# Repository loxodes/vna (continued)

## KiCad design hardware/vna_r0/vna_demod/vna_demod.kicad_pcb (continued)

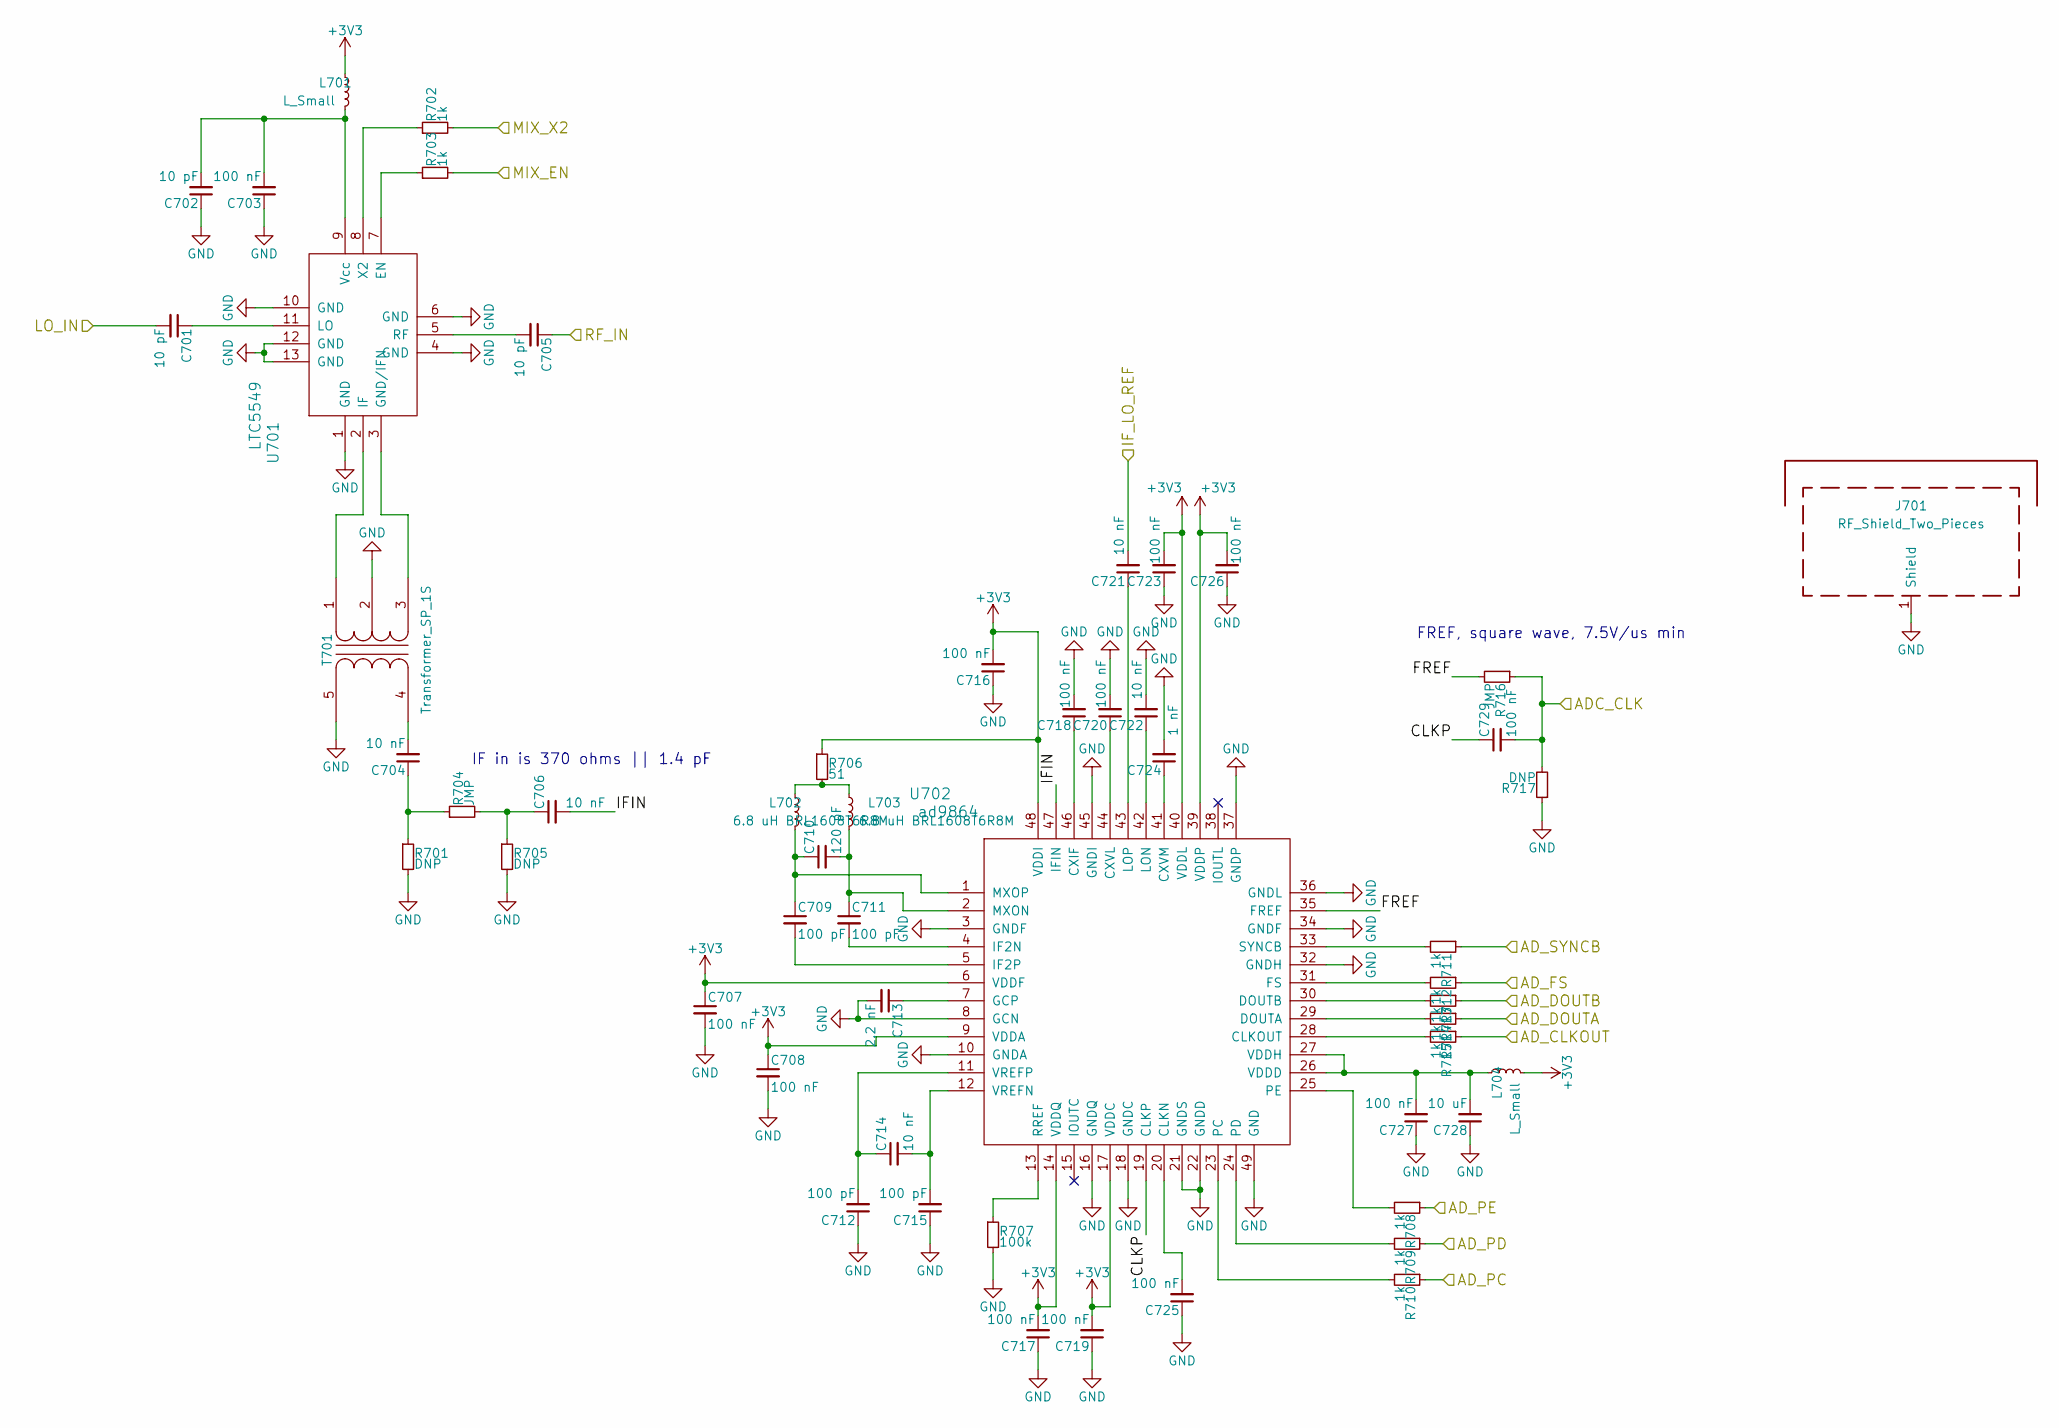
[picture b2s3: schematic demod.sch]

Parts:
C301, C302, C305: 10 pF; C_0402
C303, C307, C308, C316, C317, C318, C319, C320, C323, C325, C326, C327, C329: 100 nF; C_0402
C304, C306, C314, C321, C322: 10 nF; C_0402
C309, C311, C312, C315: 100 pF; C_0402
C310: 120 pF; C_0402
C313: 2.2 nF; C_0402
C324: 1 nF; C_0402
C328: 10 uF; C_0603
J301: RF_Shield_Two_Pieces; Laird_Technologies_BMI-S-209-F_29.36x18.50mm
L301, L304: L_Small; R_0402
L302, L303: 6.8 uH BRL1608T6R8M; R_0603
R301, R305, R317: DNP; R_0402
R302, R303, R308, R309, R310, R311, R312, R313, R314, R315: 1k; R_0402
R304, R316: JMP; R_0402
R306: 51; R_0402
R307: 100k; R_0402
T301: Transformer_SP_1S; 5LEAD_BALUN_4p83mm_3p3mm
U301: LTC5549; QFN_12_3mm2mm
U302: ad9864; QFN-48-1EP_7x7mm_Pitch0.5mm

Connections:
+3V3: C307.1, C308.1, C316.2, C317.2, C319.2, C323.2, C326.2, L301.1, L304.2, R306.1, U302.6 (VDDF), U302.9 (VDDA), U302.14 (VDDQ), U302.17 (VDDC), U302.39 (VDDP), U302.40 (VDDL), U302.48 (VDDI); also elsewhere on the board
/ADC_CLK_A: C329.2, R316.1, R317.2; also elsewhere on the board
/AD_CLKOUT: R315.1; also elsewhere on the board
/AD_DOUTA_A: R314.1; also elsewhere on the board
/AD_DOUTB: R313.1; also elsewhere on the board
/AD_FS: R312.1; also elsewhere on the board
/AD_PC: R310.1; also elsewhere on the board
/AD_PD: R309.1; also elsewhere on the board
/AD_PE_A: R308.1; also elsewhere on the board
/AD_SYNCB: R311.1; also elsewhere on the board
/IF_LO_REF_A: C321.2; also elsewhere on the board
/MIX_EN: R303.2; also elsewhere on the board
/MIX_X2: R302.2; also elsewhere on the board
/conn_power/RF_A: C305.1; also elsewhere on the board
/demod_A/CLKP: C329.1, U302.19 (CLKP)
/demod_A/FREF: R316.2, U302.35 (FREF)
/demod_A/IFIN: C306.2, U302.47 (IFIN)
/lo_synth/LO_A: C301.2; also elsewhere on the board
GND: C302.1, C303.1, C307.2, C308.2, C312.1, C313.2, C315.1, C316.1, C317.1, C318.2, C319.1, C320.2, C322.2, C323.1, C324.2, C325.1, C326.1, C327.1, C328.1, J301.1, R301.2, R305.2, R307.2, R317.1, T301.2 (PM), T301.5 (S2), U301.1 (GND), U301.4 (GND), U301.6 (GND), U301.10 (GND), U301.12 (GND), U301.13 (GND), U302.3 (GNDF), U302.8 (GCN), U302.10 (GNDA), U302.16 (GNDQ), U302.18 (GNDC), U302.21 (GNDS), U302.22 (GNDD), U302.32 (GNDH), U302.34 (GNDF), U302.36 (GNDL), U302.37 (GNDP), U302.45 (GNDI), U302.49 (GND); also elsewhere on the board
unnamed: C301.1, U301.11 (LO)
unnamed: C302.2, C303.2, L301.2, U301.9 (Vcc)
unnamed: C304.1, R301.1, R304.1
unnamed: C304.2, T301.4 (S1)
unnamed: C305.2, U301.5 (RF)
unnamed: C306.1, R304.2, R305.1
unnamed: C309.1, C310.1, L302.2, U302.1 (MXOP)
unnamed: C309.2, U302.5 (IF2P)
unnamed: C310.2, C311.1, L303.2, U302.2 (MXON)
unnamed: C311.2, U302.4 (IF2N)
unnamed: C312.2, C314.1, U302.11 (VREFP)
unnamed: C313.1, U302.7 (GCP)
unnamed: C314.2, C315.2, U302.12 (VREFN)
unnamed: C318.1, U302.46 (CXIF)
unnamed: C320.1, U302.44 (CXVL)
unnamed: C321.1, U302.43 (LOP)
unnamed: C322.1, U302.42 (LON)
unnamed: C324.1, U302.41 (CXVM)
unnamed: C325.2, U302.20 (CLKN)
unnamed: C327.2, C328.2, L304.1, U302.26 (VDDD), U302.27 (VDDH)
unnamed: L302.1, L303.1, R306.2
unnamed: R302.1, U301.8 (X2)
unnamed: R303.1, U301.7 (EN)
unnamed: R307.1, U302.13 (RREF)
unnamed: R308.2, U302.25 (PE)
unnamed: R309.2, U302.24 (PD)
unnamed: R310.2, U302.23 (PC)
unnamed: R311.2, U302.33 (SYNCB)
unnamed: R312.2, U302.31 (FS)
unnamed: R313.2, U302.30 (DOUTB)
unnamed: R314.2, U302.29 (DOUTA)
unnamed: R315.2, U302.28 (CLKOUT)
unnamed: T301.1 (PR1), U301.2 (IF)
unnamed: T301.3 (PR2), U301.3 (GND/IFN)

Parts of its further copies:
C501, C502, C505, C601, C602, C605, C701, C702, C705: 10 pF; C_0402
C503, C507, C508, C516, C517, C518, C519, C520, C523, C525, C526, C527, C529, C603, C607, C608, C616, C617, C618, C619, C620, C623, C625, C626, C627, C629, C703, C707, C708, C716, C717, C718, C719, C720, C723, C725, C726, C727, C729: 100 nF; C_0402
C504, C506, C514, C521, C522, C604, C606, C614, C621, C622, C704, C706, C714, C721, C722: 10 nF; C_0402
C509, C511, C512, C515, C609, C611, C612, C615, C709, C711, C712, C715: 100 pF; C_0402
C510, C610, C710: 120 pF; C_0402
C513, C613, C713: 2.2 nF; C_0402
C524, C624, C724: 1 nF; C_0402
C528, C628, C728: 10 uF; C_0603
J501, J601, J701: RF_Shield_Two_Pieces; Laird_Technologies_BMI-S-209-F_29.36x18.50mm
L501, L504, L601, L604, L701, L704: L_Small; R_0402
L502, L503, L602, L603, L702, L703: 6.8 uH BRL1608T6R8M; R_0603
R501, R505, R517, R601, R605, R617, R701, R705, R717: DNP; R_0402
R502, R503, R508, R509, R510, R511, R512, R513, R514, R515, R602, R603, R608, R609, R610, R611, R612, R613, R614, R615, R702, R703, R708, R709, R710, R711, R712, R713, R714, R715: 1k; R_0402
R504, R516, R604, R616, R704, R716: JMP; R_0402
R506, R606, R706: 51; R_0402
R507, R607, R707: 100k; R_0402
T501, T601, T701: Transformer_SP_1S; 5LEAD_BALUN_4p83mm_3p3mm
U501, U601, U701: LTC5549; QFN_12_3mm2mm
U502, U602, U702: ad9864; QFN-48-1EP_7x7mm_Pitch0.5mm

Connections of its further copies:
+3V3: C507.1, C508.1, C516.2, C517.2, C519.2, C523.2, C526.2, C607.1, C608.1, C616.2, C617.2, C619.2, C623.2, C626.2, C707.1, C708.1, C716.2, C717.2, C719.2, C723.2, C726.2, L501.1, L504.2, L601.1, L604.2, L701.1, L704.2, R506.1, R606.1, R706.1, U502.6 (VDDF), U502.9 (VDDA), U502.14 (VDDQ), U502.17 (VDDC), U502.39 (VDDP), U502.40 (VDDL), U502.48 (VDDI), U602.6 (VDDF), U602.9 (VDDA), U602.14 (VDDQ), U602.17 (VDDC), U602.39 (VDDP), U602.40 (VDDL), U602.48 (VDDI), U702.6 (VDDF), U702.9 (VDDA), U702.14 (VDDQ), U702.17 (VDDC), U702.39 (VDDP), U702.40 (VDDL), U702.48 (VDDI); also elsewhere on the board
/ADC_CLK_B: C529.2, R516.1, R517.2; also elsewhere on the board
/ADC_CLK_C: C629.2, R616.1, R617.2; also elsewhere on the board
/ADC_CLK_D: C729.2, R716.1, R717.2; also elsewhere on the board
/AD_DOUTA_B: R514.1; also elsewhere on the board
/AD_DOUTA_C: R614.1; also elsewhere on the board
/AD_DOUTA_D: R714.1; also elsewhere on the board
/AD_DOUTB: R513.1, R613.1, R713.1; also elsewhere on the board
/AD_PC: R510.1, R610.1, R710.1; also elsewhere on the board
/AD_PD: R509.1, R609.1, R709.1; also elsewhere on the board
/AD_PE_B: R508.1; also elsewhere on the board
/AD_PE_C: R608.1; also elsewhere on the board
/AD_PE_D: R708.1; also elsewhere on the board
/AD_SYNCB: R511.1, R611.1, R711.1; also elsewhere on the board
/IF_LO_REF_B: C521.2; also elsewhere on the board
/IF_LO_REF_C: C621.2; also elsewhere on the board
/IF_LO_REF_D: C721.2; also elsewhere on the board
/MIX_EN: R503.2, R603.2, R703.2; also elsewhere on the board
/MIX_X2: R502.2, R602.2, R702.2; also elsewhere on the board
/conn_power/RF_B: C505.1; also elsewhere on the board
/conn_power/RF_C: C605.1; also elsewhere on the board
/conn_power/RF_D: C705.1; also elsewhere on the board
/demod_B/CLKP: C529.1, U502.19 (CLKP)
/demod_B/FREF: R516.2, U502.35 (FREF)
/demod_B/IFIN: C506.2, U502.47 (IFIN)
/demod_C/CLKP: C629.1, U602.19 (CLKP)
/demod_C/FREF: R616.2, U602.35 (FREF)
/demod_C/IFIN: C606.2, U602.47 (IFIN)
/demod_D/CLKP: C729.1, U702.19 (CLKP)
/demod_D/FREF: R716.2, U702.35 (FREF)
/demod_D/IFIN: C706.2, U702.47 (IFIN)
/lo_synth/LO_B: C501.2; also elsewhere on the board
/lo_synth/LO_C: C601.2; also elsewhere on the board
/lo_synth/LO_D: C701.2; also elsewhere on the board
GND: C502.1, C503.1, C507.2, C508.2, C512.1, C513.2, C515.1, C516.1, C517.1, C518.2, C519.1, C520.2, C522.2, C523.1, C524.2, C525.1, C526.1, C527.1, C528.1, C602.1, C603.1, C607.2, C608.2, C612.1, C613.2, C615.1, C616.1, C617.1, C618.2, C619.1, C620.2, C622.2, C623.1, C624.2, C625.1, C626.1, C627.1, C628.1, C702.1, C703.1, C707.2, C708.2, C712.1, C713.2, C715.1, C716.1, C717.1, C718.2, C719.1, C720.2, C722.2, C723.1, C724.2, C725.1, C726.1, C727.1, C728.1, J501.1, J601.1, J701.1, R501.2, R505.2, R507.2, R517.1, R601.2, R605.2, R607.2, R617.1, R701.2, R705.2, R707.2, R717.1, T501.2 (PM), T501.5 (S2), T601.2 (PM), T601.5 (S2), T701.2 (PM), T701.5 (S2), U501.1 (GND), U501.4 (GND), U501.6 (GND), U501.10 (GND), U501.12 (GND), U501.13 (GND), U502.3 (GNDF), U502.8 (GCN), U502.10 (GNDA), U502.16 (GNDQ), U502.18 (GNDC), U502.21 (GNDS), U502.22 (GNDD), U502.32 (GNDH), U502.34 (GNDF), U502.36 (GNDL), U502.37 (GNDP), U502.45 (GNDI), U502.49 (GND), U601.1 (GND), U601.4 (GND), U601.6 (GND), U601.10 (GND), U601.12 (GND), U601.13 (GND), U602.3 (GNDF), U602.8 (GCN), U602.10 (GNDA), U602.16 (GNDQ), U602.18 (GNDC), U602.21 (GNDS), U602.22 (GNDD), U602.32 (GNDH), U602.34 (GNDF), U602.36 (GNDL), U602.37 (GNDP), U602.45 (GNDI), U602.49 (GND), U701.1 (GND), U701.4 (GND), U701.6 (GND), U701.10 (GND), U701.12 (GND), U701.13 (GND), U702.3 (GNDF), U702.8 (GCN), U702.10 (GNDA), U702.16 (GNDQ), U702.18 (GNDC), U702.21 (GNDS), U702.22 (GNDD), U702.32 (GNDH), U702.34 (GNDF), U702.36 (GNDL), U702.37 (GNDP), U702.45 (GNDI), U702.49 (GND); also elsewhere on the board
unnamed: C501.1, U501.11 (LO)
unnamed: C502.2, C503.2, L501.2, U501.9 (Vcc)
unnamed: C504.1, R501.1, R504.1
unnamed: C504.2, T501.4 (S1)
unnamed: C505.2, U501.5 (RF)
unnamed: C506.1, R504.2, R505.1
unnamed: C509.1, C510.1, L502.2, U502.1 (MXOP)
unnamed: C509.2, U502.5 (IF2P)
unnamed: C510.2, C511.1, L503.2, U502.2 (MXON)
unnamed: C511.2, U502.4 (IF2N)
unnamed: C512.2, C514.1, U502.11 (VREFP)
unnamed: C513.1, U502.7 (GCP)
unnamed: C514.2, C515.2, U502.12 (VREFN)
unnamed: C518.1, U502.46 (CXIF)
unnamed: C520.1, U502.44 (CXVL)
unnamed: C521.1, U502.43 (LOP)
unnamed: C522.1, U502.42 (LON)
unnamed: C524.1, U502.41 (CXVM)
unnamed: C525.2, U502.20 (CLKN)
unnamed: C527.2, C528.2, L504.1, U502.26 (VDDD), U502.27 (VDDH)
unnamed: C601.1, U601.11 (LO)
unnamed: C602.2, C603.2, L601.2, U601.9 (Vcc)
unnamed: C604.1, R601.1, R604.1
unnamed: C604.2, T601.4 (S1)
unnamed: C605.2, U601.5 (RF)
unnamed: C606.1, R604.2, R605.1
unnamed: C609.1, C610.1, L602.2, U602.1 (MXOP)
unnamed: C609.2, U602.5 (IF2P)
unnamed: C610.2, C611.1, L603.2, U602.2 (MXON)
unnamed: C611.2, U602.4 (IF2N)
unnamed: C612.2, C614.1, U602.11 (VREFP)
unnamed: C613.1, U602.7 (GCP)
unnamed: C614.2, C615.2, U602.12 (VREFN)
unnamed: C618.1, U602.46 (CXIF)
unnamed: C620.1, U602.44 (CXVL)
unnamed: C621.1, U602.43 (LOP)
unnamed: C622.1, U602.42 (LON)
unnamed: C624.1, U602.41 (CXVM)
unnamed: C625.2, U602.20 (CLKN)
unnamed: C627.2, C628.2, L604.1, U602.26 (VDDD), U602.27 (VDDH)
unnamed: C701.1, U701.11 (LO)
unnamed: C702.2, C703.2, L701.2, U701.9 (Vcc)
unnamed: C704.1, R701.1, R704.1
unnamed: C704.2, T701.4 (S1)
unnamed: C705.2, U701.5 (RF)
unnamed: C706.1, R704.2, R705.1
unnamed: C709.1, C710.1, L702.2, U702.1 (MXOP)
unnamed: C709.2, U702.5 (IF2P)
unnamed: C710.2, C711.1, L703.2, U702.2 (MXON)
unnamed: C711.2, U702.4 (IF2N)
unnamed: C712.2, C714.1, U702.11 (VREFP)
unnamed: C713.1, U702.7 (GCP)
unnamed: C714.2, C715.2, U702.12 (VREFN)
unnamed: C718.1, U702.46 (CXIF)
unnamed: C720.1, U702.44 (CXVL)
unnamed: C721.1, U702.43 (LOP)
unnamed: C722.1, U702.42 (LON)
unnamed: C724.1, U702.41 (CXVM)
unnamed: C725.2, U702.20 (CLKN)
unnamed: C727.2, C728.2, L704.1, U702.26 (VDDD), U702.27 (VDDH)
unnamed: L502.1, L503.1, R506.2
unnamed: L602.1, L603.1, R606.2
unnamed: L702.1, L703.1, R706.2
unnamed: R502.1, U501.8 (X2)
unnamed: R503.1, U501.7 (EN)
unnamed: R507.1, U502.13 (RREF)
unnamed: R508.2, U502.25 (PE)
unnamed: R509.2, U502.24 (PD)
unnamed: R510.2, U502.23 (PC)
unnamed: R511.2, U502.33 (SYNCB)
unnamed: R512.2, U502.31 (FS)
unnamed: R513.2, U502.30 (DOUTB)
unnamed: R514.2, U502.29 (DOUTA)
unnamed: R515.2, U502.28 (CLKOUT)
unnamed: R602.1, U601.8 (X2)
unnamed: R603.1, U601.7 (EN)
unnamed: R607.1, U602.13 (RREF)
unnamed: R608.2, U602.25 (PE)
unnamed: R609.2, U602.24 (PD)
unnamed: R610.2, U602.23 (PC)
unnamed: R611.2, U602.33 (SYNCB)
unnamed: R612.2, U602.31 (FS)
unnamed: R613.2, U602.30 (DOUTB)
unnamed: R614.2, U602.29 (DOUTA)
unnamed: R615.2, U602.28 (CLKOUT)
unnamed: R702.1, U701.8 (X2)
unnamed: R703.1, U701.7 (EN)
unnamed: R707.1, U702.13 (RREF)
unnamed: R708.2, U702.25 (PE)
unnamed: R709.2, U702.24 (PD)
unnamed: R710.2, U702.23 (PC)
unnamed: R711.2, U702.33 (SYNCB)
unnamed: R712.2, U702.31 (FS)
unnamed: R713.2, U702.30 (DOUTB)
unnamed: R714.2, U702.29 (DOUTA)
unnamed: R715.2, U702.28 (CLKOUT)
unnamed: T501.1 (PR1), U501.2 (IF)
unnamed: T501.3 (PR2), U501.3 (GND/IFN)
unnamed: T601.1 (PR1), U601.2 (IF)
unnamed: T601.3 (PR2), U601.3 (GND/IFN)
unnamed: T701.1 (PR1), U701.2 (IF)
unnamed: T701.3 (PR2), U701.3 (GND/IFN)

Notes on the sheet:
FREF, square wave, 7.5V/us min
IF in is 370 ohms || 1.4 pF

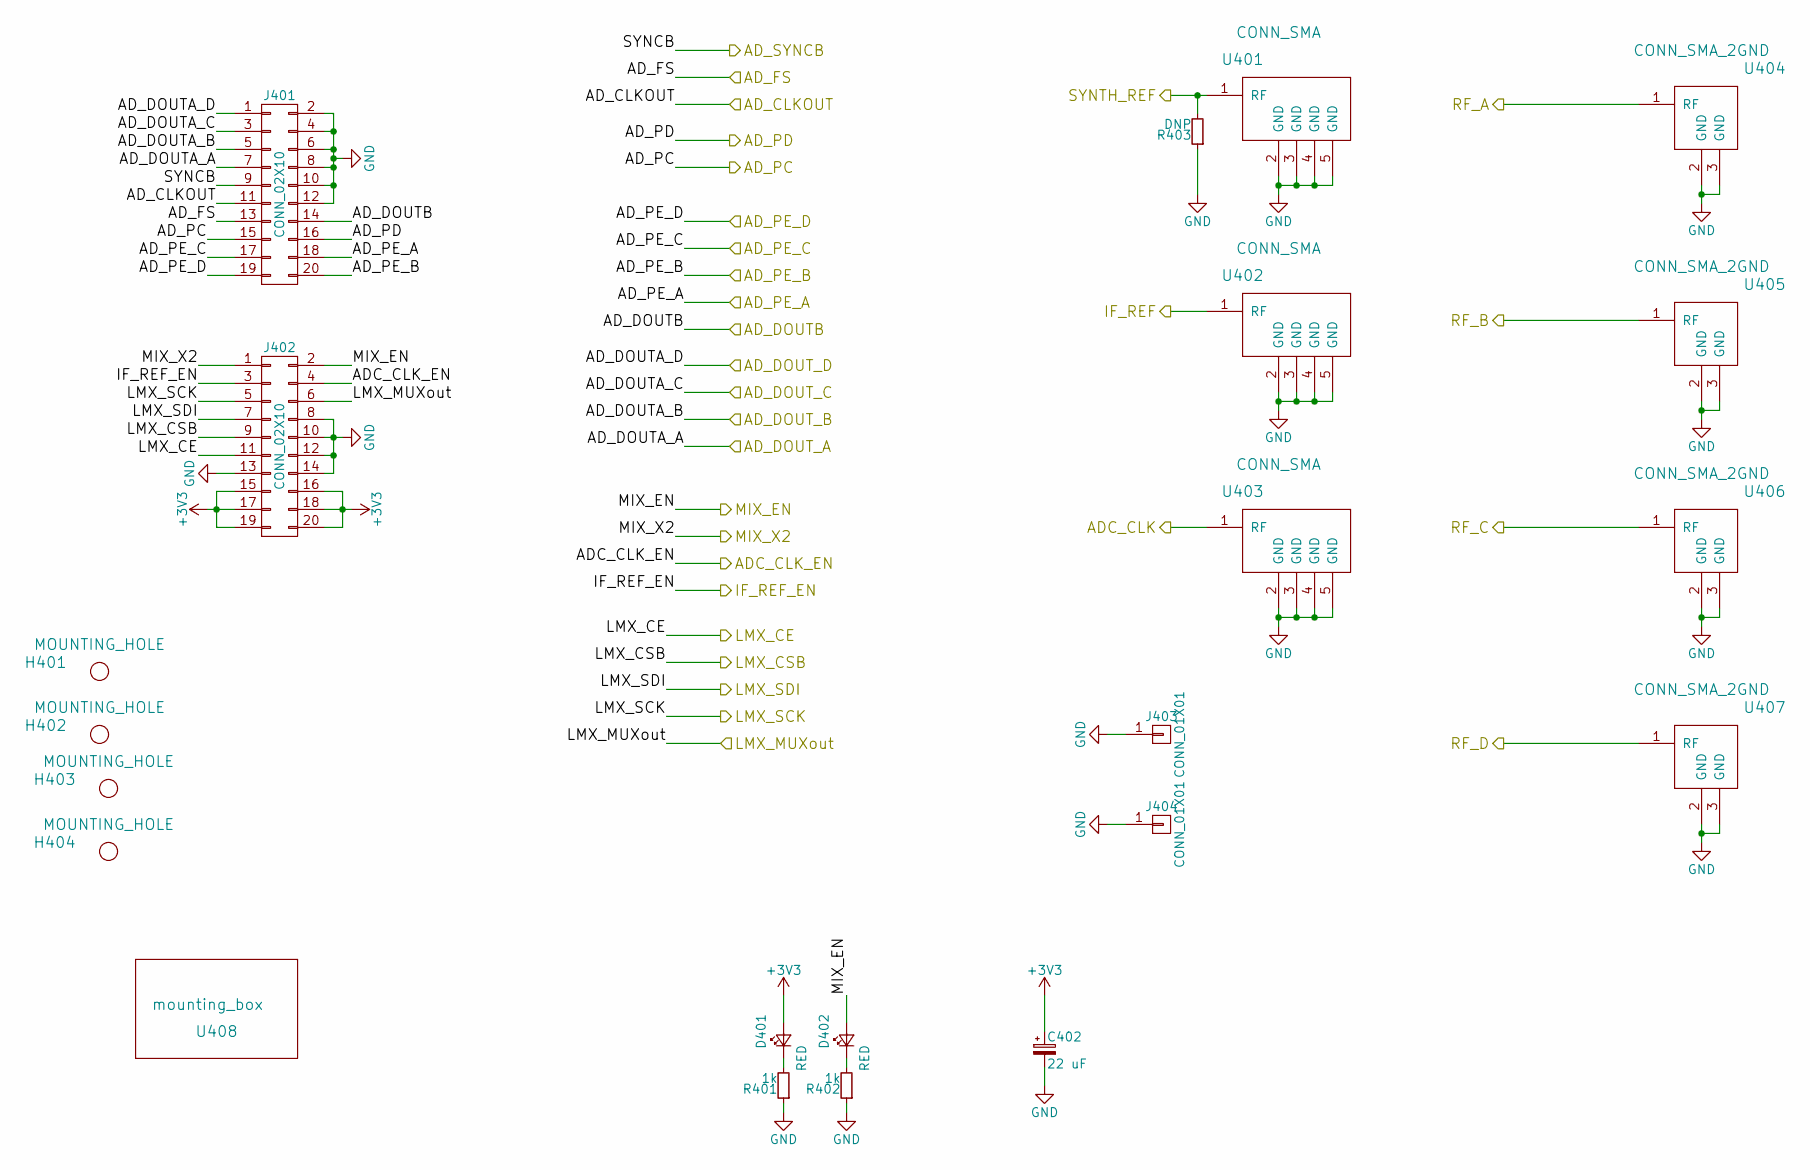
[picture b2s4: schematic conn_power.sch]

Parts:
C402: 22 uF; c_elec_10x10
D401, D402: RED; LED_0603
H401, H402, H403, H404: MOUNTING_HOLE; MountingHole_2-7mm
J401, J402: CONN_02X10; IDC_Header_Straight_20pins
J403, J404: CONN_01X01; Pin_Header_Straight_1x01
R401, R402: 1k; R_0402
R403: DNP; R_0402
U401, U402, U403: CONN_SMA; 732511150_sma_thin
U404, U405, U406, U407: CONN_SMA_2GND; SMA_901-10512_30MIL_OSHFR408_CPW_LAUNCH
U408: mounting_box; snail

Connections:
+3V3: C402.1, D401.2 (A), J402.15, J402.16, J402.17, J402.18, J402.19, J402.20; also elsewhere on the board
/ADC_CLK: U403.1 (RF); also elsewhere on the board
/ADC_CLK_EN: J402.4; also elsewhere on the board
/AD_CLKOUT: J401.11; also elsewhere on the board
/AD_DOUTA_A: J401.7; also elsewhere on the board
/AD_DOUTA_B: J401.5; also elsewhere on the board
/AD_DOUTA_C: J401.3; also elsewhere on the board
/AD_DOUTA_D: J401.1; also elsewhere on the board
/AD_DOUTB: J401.14; also elsewhere on the board
/AD_FS: J401.13; also elsewhere on the board
/AD_PC: J401.15; also elsewhere on the board
/AD_PD: J401.16; also elsewhere on the board
/AD_PE_A: J401.18; also elsewhere on the board
/AD_PE_B: J401.20; also elsewhere on the board
/AD_PE_C: J401.17; also elsewhere on the board
/AD_PE_D: J401.19; also elsewhere on the board
/AD_SYNCB: J401.9; also elsewhere on the board
/IF_REF: U402.1 (RF); also elsewhere on the board
/IF_REF_EN: J402.3; also elsewhere on the board
/LMX_CE: J402.11; also elsewhere on the board
/LMX_CSB: J402.9; also elsewhere on the board
/LMX_MUXout: J402.6; also elsewhere on the board
/LMX_SCK: J402.5; also elsewhere on the board
/LMX_SDI: J402.7; also elsewhere on the board
/MIX_EN: D402.2 (A), J402.2; also elsewhere on the board
/MIX_X2: J402.1; also elsewhere on the board
/SYNTH_FREF: R403.2, U401.1 (RF); also elsewhere on the board
/conn_power/RF_A: U404.1 (RF); also elsewhere on the board
/conn_power/RF_B: U405.1 (RF); also elsewhere on the board
/conn_power/RF_C: U406.1 (RF); also elsewhere on the board
/conn_power/RF_D: U407.1 (RF); also elsewhere on the board
GND: C402.2, J401.2, J401.4, J401.6, J401.8, J401.10, J401.12, J402.8, J402.10, J402.12, J402.13, J402.14, J403.1, J404.1, R401.1, R402.1, R403.1, U401.2 (GND), U401.3 (GND), U401.4 (GND), U401.5 (GND), U402.2 (GND), U402.3 (GND), U402.4 (GND), U402.5 (GND), U403.2 (GND), U403.3 (GND), U403.4 (GND), U403.5 (GND), U404.2 (GND), U404.3 (GND), U405.2 (GND), U405.3 (GND), U406.2 (GND), U406.3 (GND), U407.2 (GND), U407.3 (GND); also elsewhere on the board
unnamed: D401.1 (K), R401.2
unnamed: D402.1 (K), R402.2

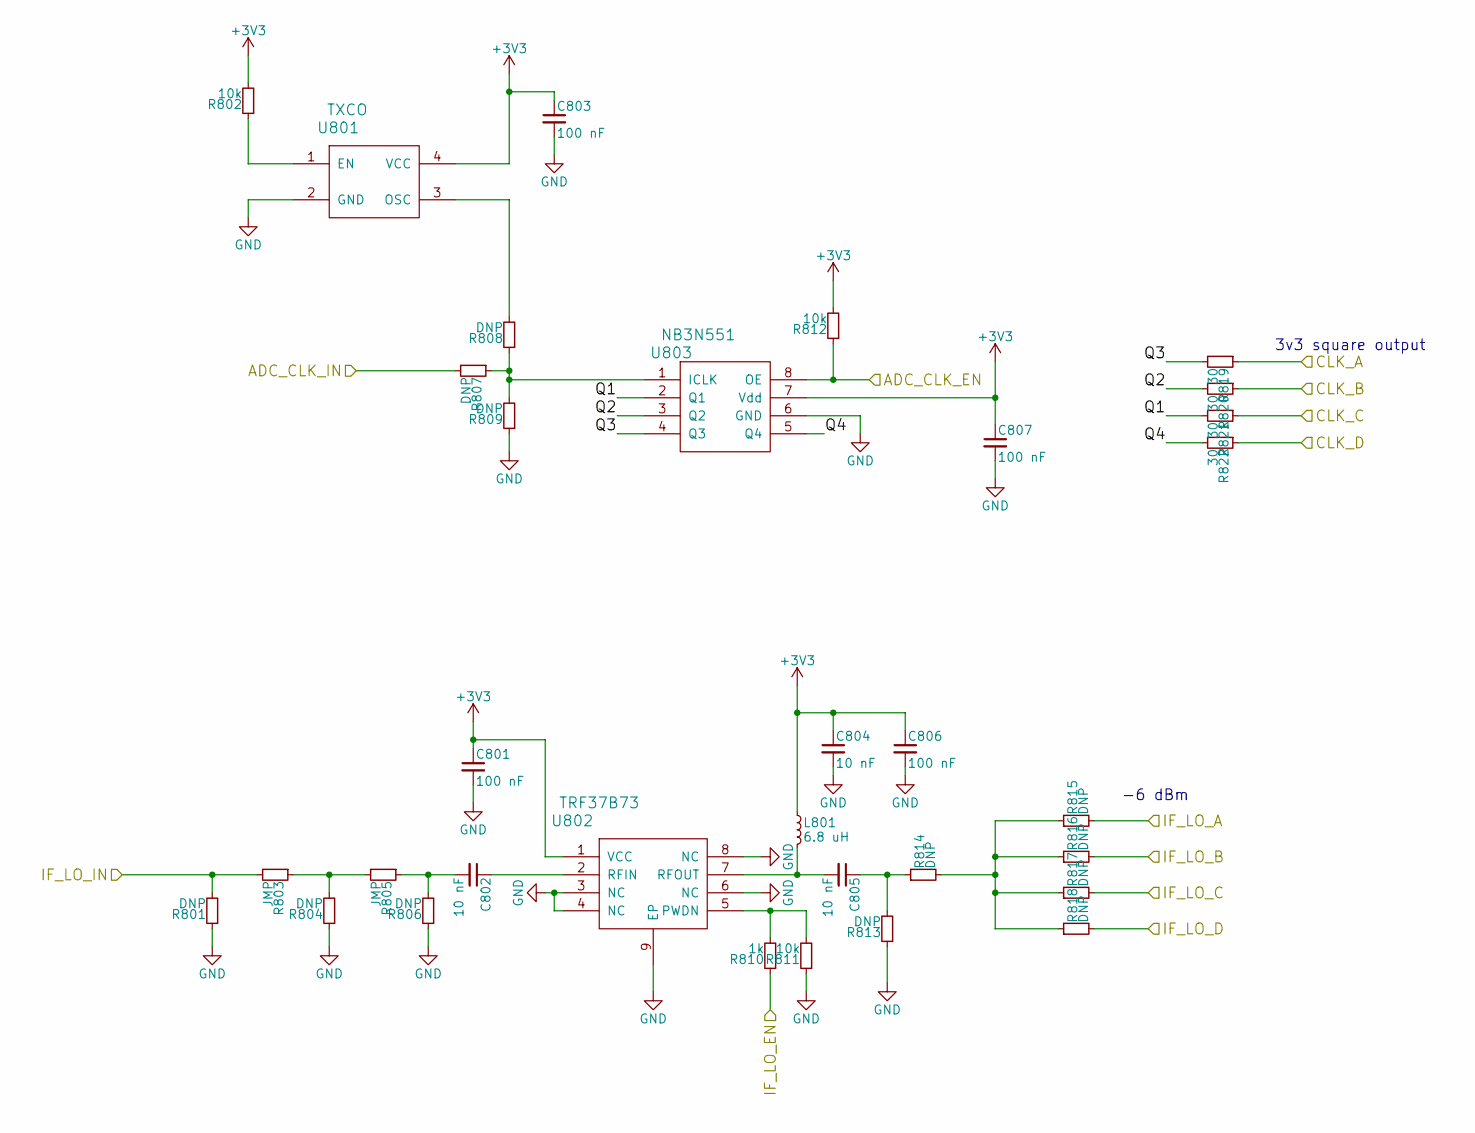
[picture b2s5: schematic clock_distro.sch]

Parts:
C801, C803, C806, C807: 100 nF; C_0402
C802, C804, C805: 10 nF; C_0402
L801: 6.8 uH; R_0603
R801, R804, R806, R807, R808, R809, R813, R814, R815, R816, R817, R818: DNP; R_0402
R802, R811, R812: 10k; R_0402
R803, R805: JMP; R_0402
R810: 1k; R_0402
R819, R820, R821, R822: 30; R_0402
U801: TXCO; crystal_FA238-TSX3225
U802: TRF37B73; DFN-8-1EP_2x2mm_Pitch0.5mm
U803: NB3N551; SOIC-8_3.9x4.9mm_Pitch1.27mm

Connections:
+3V3: C801.1, C803.1, C804.1, C806.1, C807.1, L801.1, R802.2, R812.2, U801.4 (VCC), U802.1 (VCC), U803.7 (Vdd); also elsewhere on the board
/ADC_CLK: R807.2; also elsewhere on the board
/ADC_CLK_A: R819.1; also elsewhere on the board
/ADC_CLK_B: R820.1; also elsewhere on the board
/ADC_CLK_C: R821.1; also elsewhere on the board
/ADC_CLK_D: R822.1; also elsewhere on the board
/ADC_CLK_EN: R812.1, U803.8 (OE); also elsewhere on the board
/IF_LO_REF_A: R815.2; also elsewhere on the board
/IF_LO_REF_B: R816.2; also elsewhere on the board
/IF_LO_REF_C: R817.2; also elsewhere on the board
/IF_LO_REF_D: R818.2; also elsewhere on the board
/IF_REF: R801.2, R803.2; also elsewhere on the board
/IF_REF_EN: R810.1; also elsewhere on the board
/clock_distro/Q1: R821.2, U803.2 (Q1)
/clock_distro/Q2: R820.2, U803.3 (Q2)
/clock_distro/Q3: R819.2, U803.4 (Q3)
/clock_distro/Q4: R822.2, U803.5 (Q4)
GND: C801.2, C803.2, C804.2, C806.2, C807.2, R801.1, R804.1, R806.1, R809.1, R811.1, R813.1, U801.2 (GND), U802.3 (NC), U802.4 (NC), U802.6 (NC), U802.8 (NC), U802.9 (EP), U803.6 (GND); also elsewhere on the board
unnamed: C802.1, U802.2 (RFIN)
unnamed: C802.2, R805.1, R806.2
unnamed: C805.1, R813.2, R814.1
unnamed: C805.2, L801.2, U802.7 (RFOUT)
unnamed: R802.1, U801.1 (EN)
unnamed: R803.1, R804.2, R805.2
unnamed: R807.1, R808.1, R809.2, U803.1 (ICLK)
unnamed: R808.2, U801.3 (OSC)
unnamed: R810.2, R811.2, U802.5 (PWDN)
unnamed: R814.2, R815.1, R816.1, R817.1, R818.1

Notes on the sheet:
3v3 square output
-6 dBm

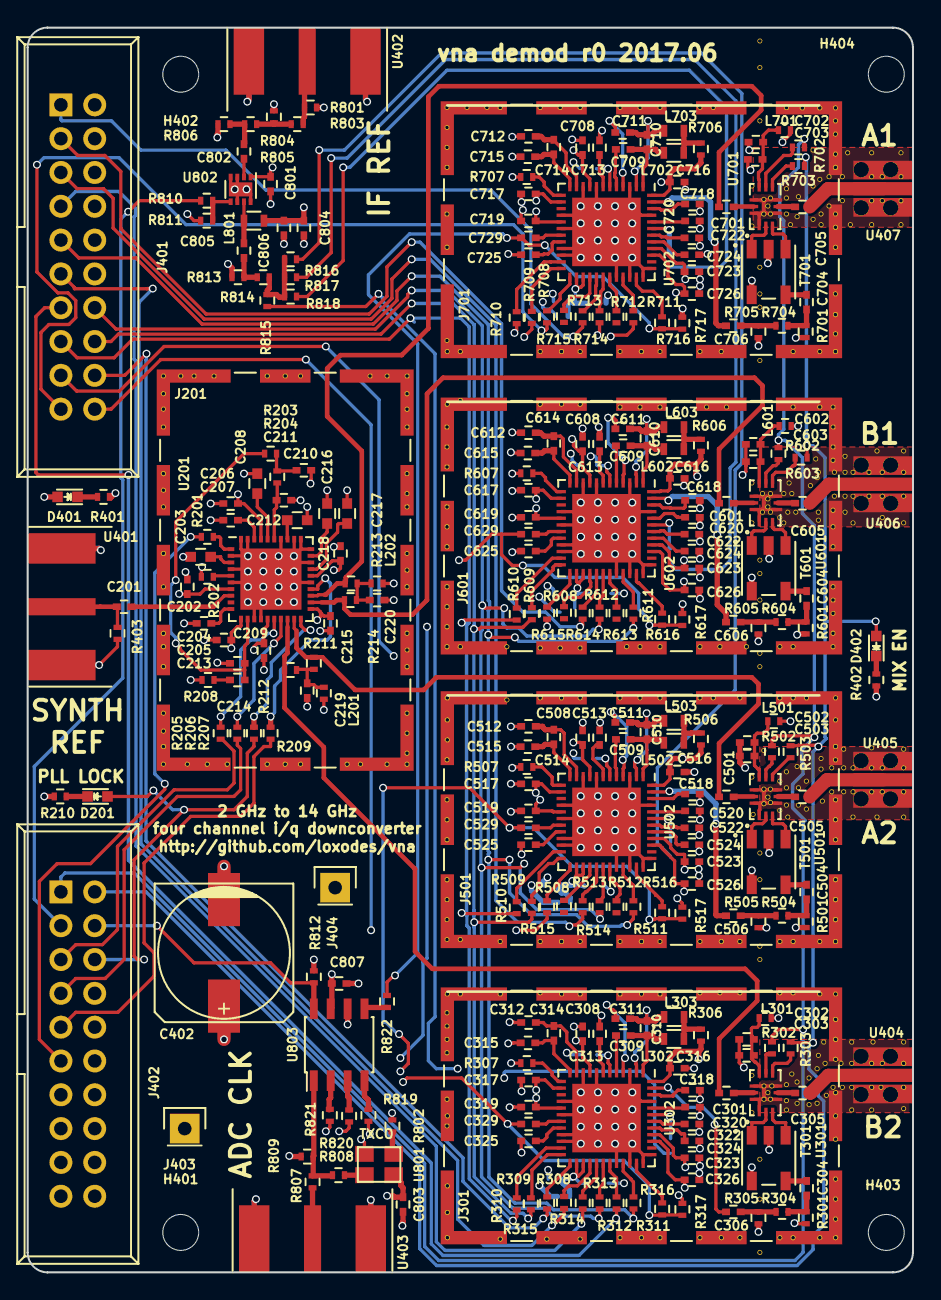
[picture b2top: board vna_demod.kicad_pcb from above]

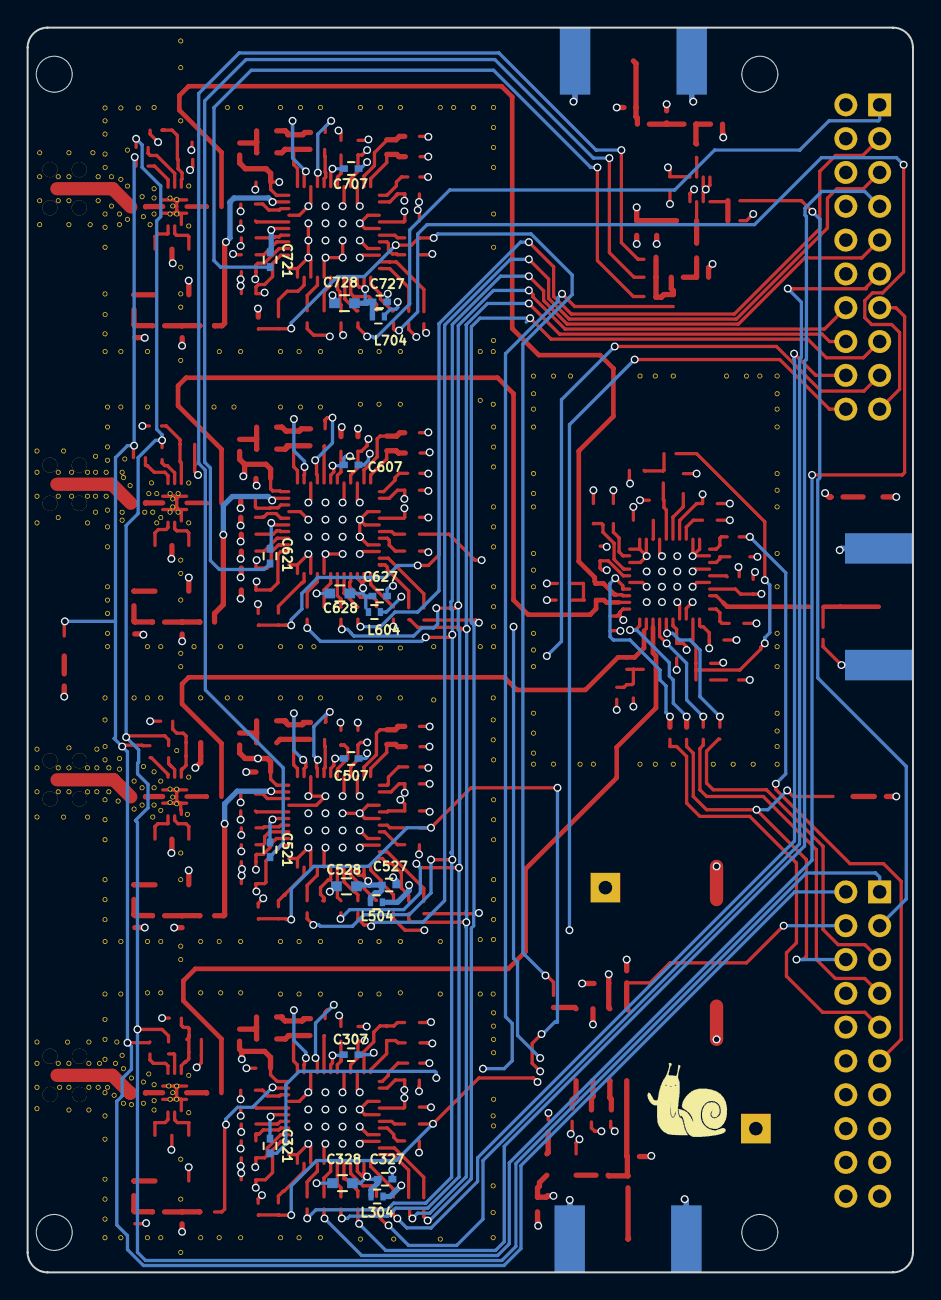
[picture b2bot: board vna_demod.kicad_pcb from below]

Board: 4 copper layers, 66.5 x 93.5 mm, 310 parts (21 on the bottom side), 229 nets.
